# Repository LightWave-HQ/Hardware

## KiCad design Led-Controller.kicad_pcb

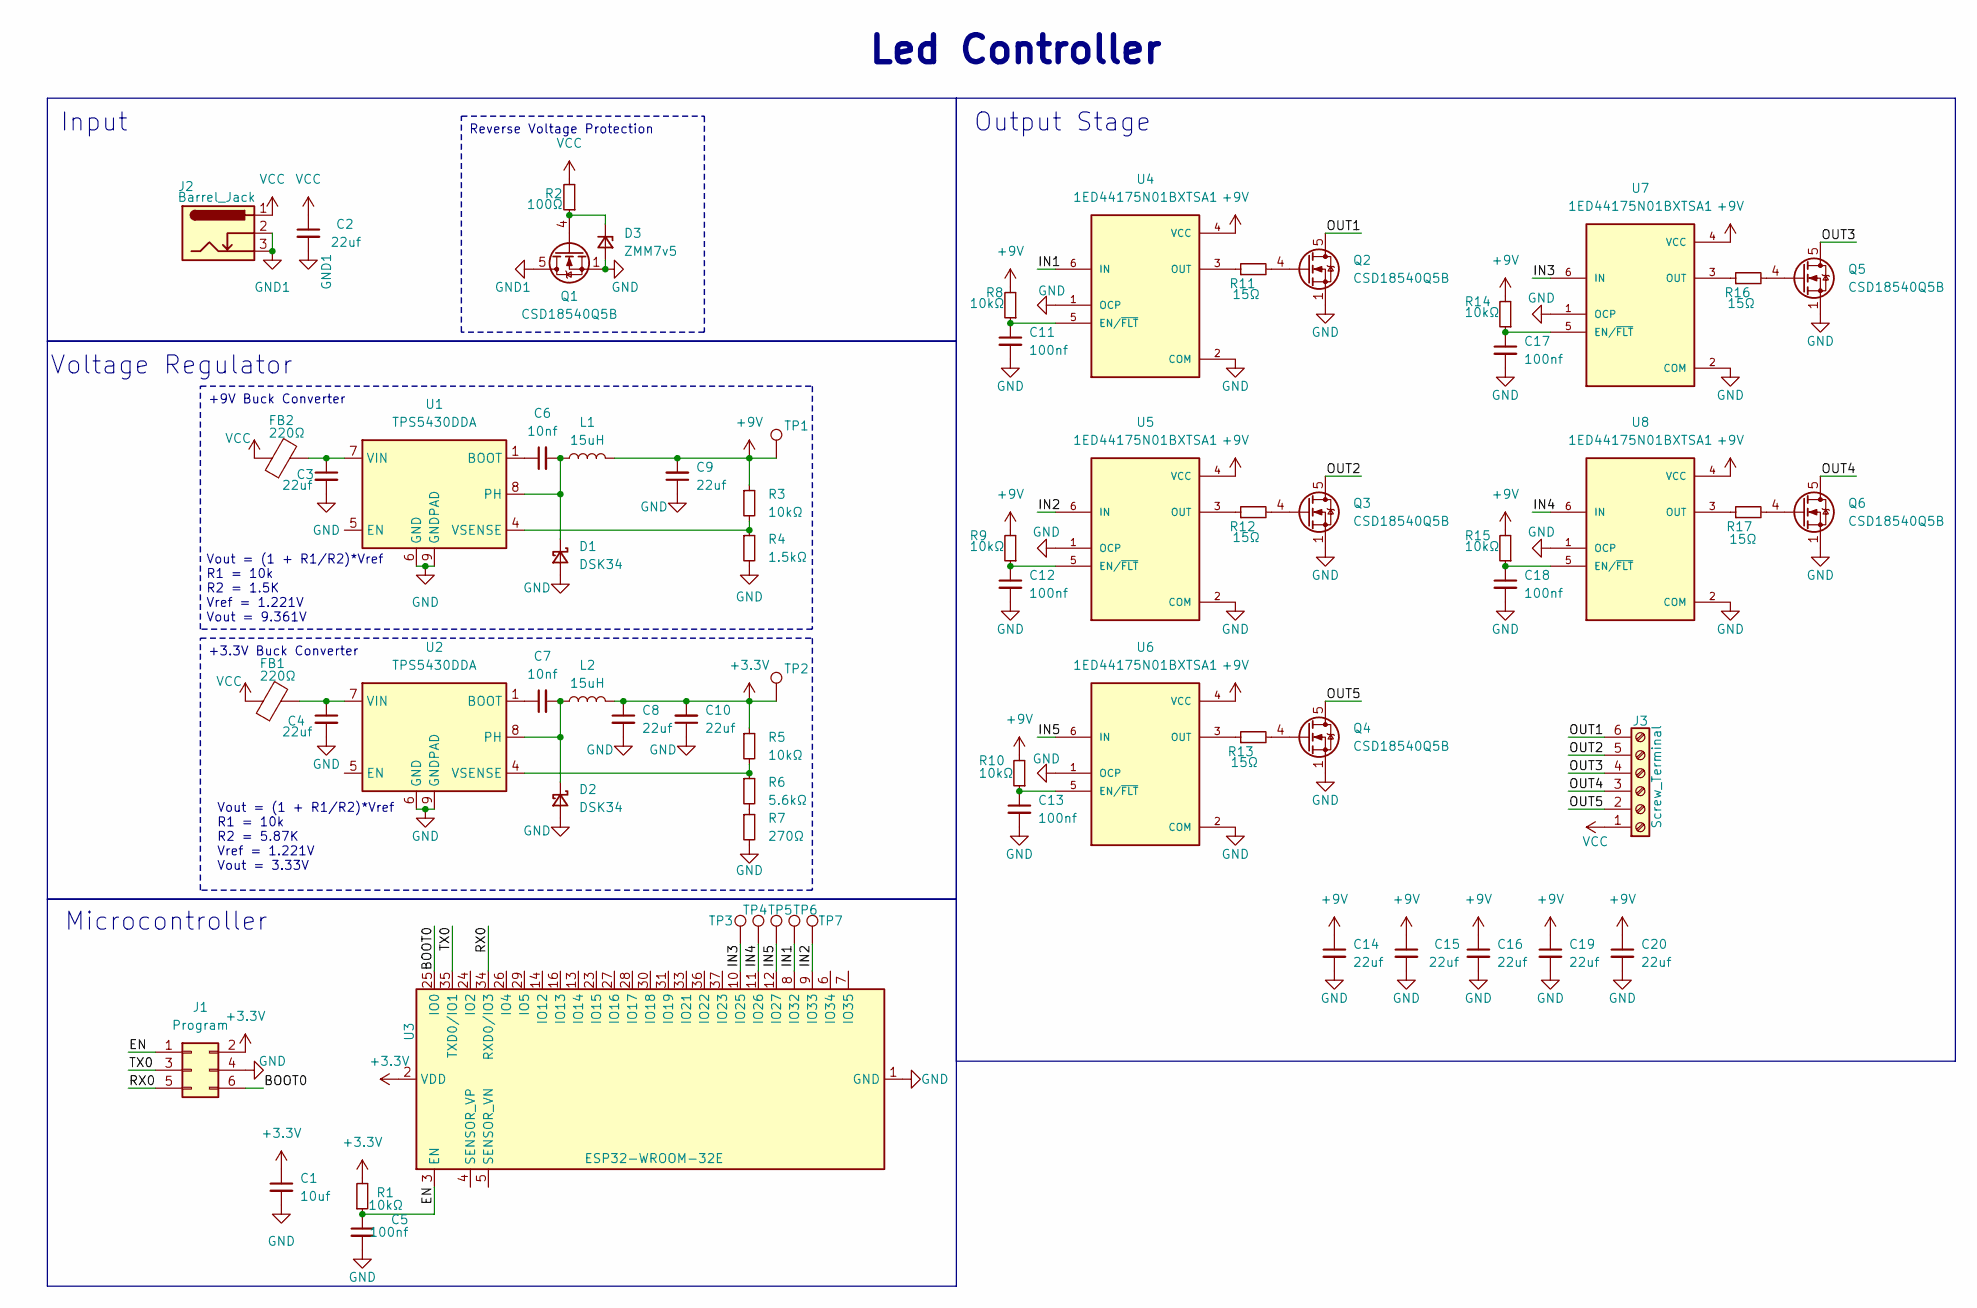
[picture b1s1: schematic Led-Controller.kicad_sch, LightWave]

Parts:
C1: 10uf; C_0402_1005Metric
C2, C3, C4, C8, C9, C10, C14, C15, C16, C19, C20: 22uf; C_0805_2012Metric
C5, C11, C12, C13, C17, C18: 100nf; C_0402_1005Metric
C6, C7: 10nf; C_0402_1005Metric
D1, D2: DSK34; D_SOD-123
D3: ZMM7v5; D_MiniMELF
FB1, FB2: 220Ω; R_0805_2012Metric
J1: Program; PinHeader_2x03_P1.27mm_Vertical
J2: Barrel_Jack; BarrelJack_GCT_DCJ200-10-A_Horizontal
J3: Screw_Terminal; TerminalBlock_bornier-6_P5.08mm
L1, L2: 15uH; L_Bourns-SRN8040_8x8.15mm
Q1, Q2, Q3, Q4, Q5, Q6: CSD18540Q5B; TDSON-8-1
R1, R3, R5, R8, R9, R10, R14, R15: 10kΩ; R_0402_1005Metric
R2: 100Ω; R_0402_1005Metric
R4: 1.5kΩ; R_0402_1005Metric
R6: 5.6kΩ; R_0402_1005Metric
R7: 270Ω; R_0402_1005Metric
R11, R12, R13, R16, R17: 15Ω; R_0402_1005Metric
TP1, TP2, TP3, TP4, TP5, TP6, TP7: TestPoint_Pad_D1.0mm
U1, U2: TPS5430DDA; TI_SO-PowerPAD-8_ThermalVias
U3: ESP32-WROOM-32E; ESP32-WROOM-32D
U4, U5, U6, U7, U8: 1ED44175N01BXTSA1; PARTREV 1.0

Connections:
+3.3V: C1.1, C8.1, C10.2, J1.2, L2.2, R1.2, R5.1, TP2.1, U3.2 (VDD)
+9V: C9.2, C14.1, C15.1, C16.1, C19.1, C20.1, L1.2, R3.1, R8.2, R9.2, R10.2, R14.2, R15.2, TP1.1, U4.4 (VCC), U5.4 (VCC), U6.4 (VCC), U7.4 (VCC), U8.4 (VCC)
/BOOT0: J1.6, U3.25 (IO0)
/EN: C5.1, J1.1, R1.1, U3.3 (EN)
/IN1: TP6.1, U3.8 (IO32), U4.6 (IN)
/IN2: TP7.1, U3.9 (IO33), U5.6 (IN)
/IN3: TP3.1, U3.10 (IO25), U7.6 (IN)
/IN4: TP4.1, U3.11 (IO26), U8.6 (IN)
/IN5: TP5.1, U3.12 (IO27), U6.6 (IN)
/OUT1: J3.6, Q2.5 (D)
/OUT2: J3.5, Q3.5 (D)
/OUT3: J3.4, Q5.5 (D)
/OUT4: J3.3, Q6.5 (D)
/OUT5: J3.2, Q4.5 (D)
/RX0: J1.5, U3.34 (RXD0/IO3)
/TX0: J1.3, U3.35 (TXD0/IO1)
GND: C1.2, C3.2, C4.2, C5.2, C8.2, C9.1, C10.1, C11.2, C12.2, C13.2, C14.2, C15.2, C16.2, C17.2, C18.2, C19.2, C20.2, D1.2 (A), D2.2 (A), D3.2 (A), J1.4, Q1.1 (S), Q1.2 (S), Q1.3 (S), Q2.1 (S), Q2.2 (S), Q2.3 (S), Q3.1 (S), Q3.2 (S), Q3.3 (S), Q4.1 (S), Q4.2 (S), Q4.3 (S), Q5.1 (S), Q5.2 (S), Q5.3 (S), Q6.1 (S), Q6.2 (S), Q6.3 (S), R4.2, R7.2, U1.6 (GND), U1.9 (GNDPAD), U2.6 (GND), U2.9 (GNDPAD), U3.1 (GND), U3.15 (GND), U3.38 (GND), U3.39 (GND), U4.1 (OCP), U4.2 (COM), U5.1 (OCP), U5.2 (COM), U6.1 (OCP), U6.2 (COM), U7.1 (OCP), U7.2 (COM), U8.1 (OCP), U8.2 (COM)
GND1: C2.2, J2.2, J2.3, Q1.5 (D)
unnamed: C6.2, D1.1 (K), L1.1, U1.8 (PH)
unnamed: C7.2, D2.1 (K), L2.1, U2.8 (PH)
unnamed: D3.1 (K), Q1.4 (G), R2.1
unnamed: Q2.4 (G), R11.2
unnamed: Q3.4 (G), R12.2
unnamed: Q4.4 (G), R13.2
unnamed: Q5.4 (G), R16.2
unnamed: Q6.4 (G), R17.2
unnamed: R6.2, R7.1
unnamed: C6.1, U1.1 (BOOT)
unnamed: C3.1, FB2.2, U1.7 (VIN)
unnamed: R3.2, R4.1, U1.4 (VSENSE)
unnamed: C7.1, U2.1 (BOOT)
unnamed: C4.1, FB1.2, U2.7 (VIN)
unnamed: R5.2, R6.1, U2.4 (VSENSE)
unnamed: C11.1, R8.1, U4.5 (EN/~FLT)
unnamed: R11.1, U4.3 (OUT)
unnamed: C12.1, R9.1, U5.5 (EN/~FLT)
unnamed: R12.1, U5.3 (OUT)
unnamed: C13.1, R10.1, U6.5 (EN/~FLT)
unnamed: R13.1, U6.3 (OUT)
unnamed: C17.1, R14.1, U7.5 (EN/~FLT)
unnamed: R16.1, U7.3 (OUT)
unnamed: C18.1, R15.1, U8.5 (EN/~FLT)
unnamed: R17.1, U8.3 (OUT)
VCC: C2.1, FB1.1, FB2.1, J2.1, J3.1, R2.2

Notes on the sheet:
Reverse Voltage Protection
+9V Buck Converter
+3.3V Buck Converter
Input
Vout = (1 + R1/R2)*Vref R1 = 10k R2 = 1.5K Vref = 1.221V Vout = 9.361V
Voltage Regulator
Output Stage
Microcontroller
Vout = (1 + R1/R2)*Vref R1 = 10k R2 = 5.87K Vref = 1.221V Vout = 3.33V
Led Controller

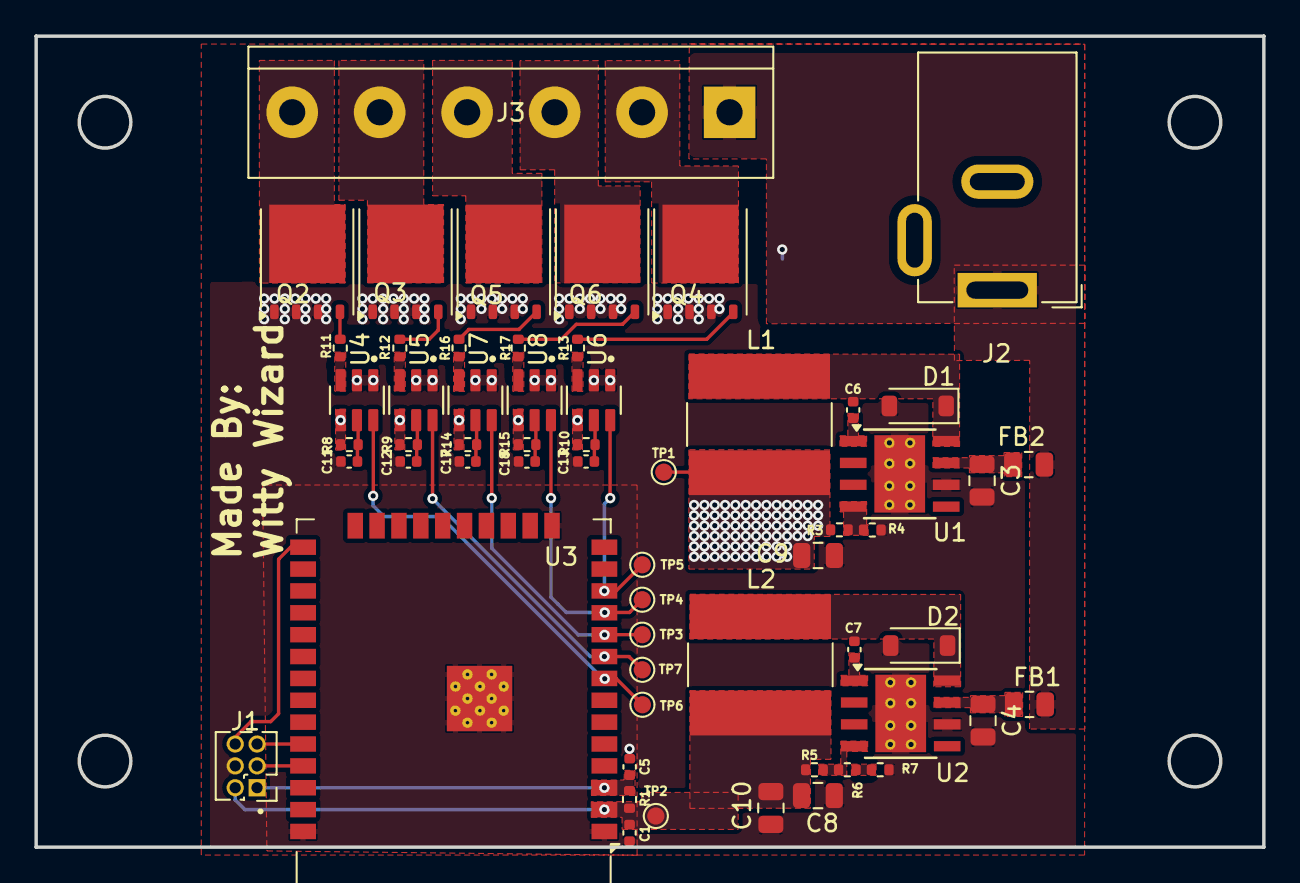
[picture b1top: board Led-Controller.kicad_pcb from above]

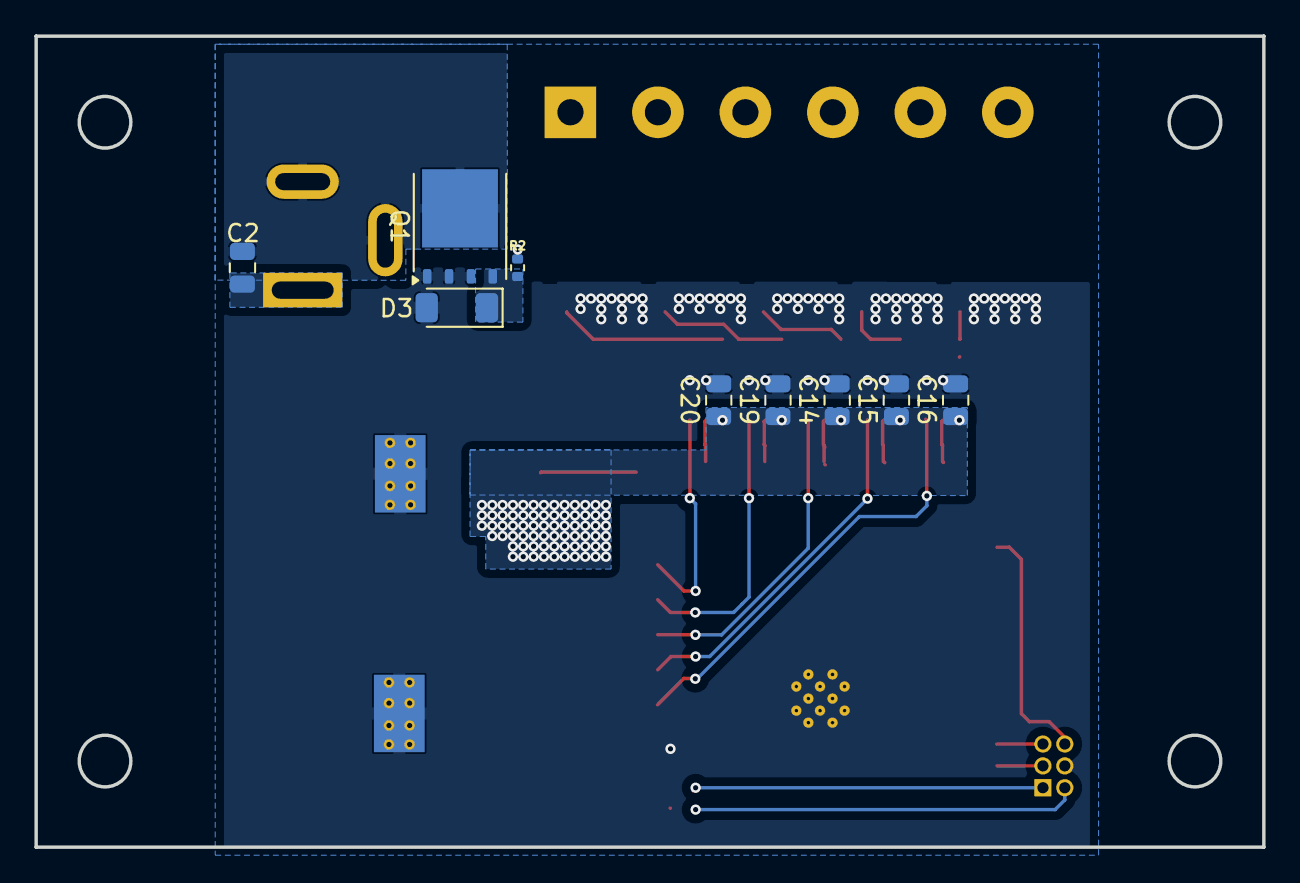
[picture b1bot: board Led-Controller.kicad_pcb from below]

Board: 2 copper layers, 71.3 x 47.1 mm, 68 parts (9 on the bottom side), 44 nets.

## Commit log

2024-12-27 Hardware with Mosfets
2025-01-17 Fixed: Pin assignment
2025-01-17 Added: Pull up resistor for EN pin
2025-01-17 Added: the missing trace connecting Driver to MOSFET
2025-01-17 Added: N channel mosfet in place of P channel mosfet
2025-01-17 Added: N channel mosfet in place of P channel mosfet (#16)
2025-01-17 Fixed: Missing trace of RC circuit connecting to the gate driver
2025-01-17 Fixed: Missing trace of RC circuit connecting to the gate driver (#17)
2025-01-17 Changed Componentes to smaller Footprint
2025-01-17 Changed Components to smaller Footprint (#18)
2025-01-18 Added: Reverse voltage protection
2025-01-18 Added: Reverse voltage protection (#19)
2025-01-18 Added: 6 Pin IDC Connector for Programming
2025-01-18 Added: 6 Pin IDC Connector for Programming (#20)
2025-01-18 Added: Switching Regulator Schematic
2025-01-21 Changed License to CERN OHL
2025-01-21 Added: Final Layout for the Switching regulator along with the overall PCB layout
2025-01-21 Added: Switching Regulator (#21)
    * Added: Switching Regulator Schematic
    * Added: Final Layout for the Switching regulator along with the overall PCB layout
2025-01-21 Added: Ferrite bead for conduction EMI filtering
2025-01-21 Added: Ferrite bead for conduction EMI filtering (#23)
2025-01-22 Did basic routing for voltage regulators
2025-01-22 Final Layout of PCB verion 2 alpha
2025-01-22 Final Layout of alpha version 2 (#24)
    * Did basic routing for voltage regulators
    * Final Layout of PCB version 2 alpha
2025-02-26 Added: New Outline file
2025-03-09 Fixed: Build Pipeline
    Updated: Kicad version from v8.0.0 to v9.0.0
